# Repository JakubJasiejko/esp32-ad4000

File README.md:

# esp32-ad4000

Driver for the `AD4000` ADC on ESP32. The library handles device configuration and fast raw sample reads over SPI.

## Features
- initialize the device and SPI bus
- configure the control register
- prepare the interface before measurement
- fast `uint16_t` raw data reads

## Dependencies
- `esp32-spi2-bus`

## Files
- `include/ad4000.h`
- `src/ad4000.c`

## Quick start
```c
#include "ad4000.h"

void app_main(void)
{
    spi2_init_bus(SPI2_BUS1, SPI3_HOST, AD4000_PIN_SDI, AD4000_PIN_SDO, AD4000_PIN_SCLK);

    int adc = -1;
    ad4000_init(SPI2_BUS1, &adc, 0, GPIO_NUM_NC, AD4000_PIN_CNV, AD4000_SPI_CLK_HZ, 0);
    ad4000_prepareBeforeMeasurement(adc, AD4000_PIN_SDI);
    uint16_t raw = ad4000_getRawData(adc, AD4000_PIN_CNV);
    (void)raw;
}
```

See `examples/basic_usage/basic_usage.c` for a complete example.

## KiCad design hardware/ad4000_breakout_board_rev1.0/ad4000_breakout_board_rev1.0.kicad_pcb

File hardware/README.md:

# Hardware — esp32-ad4000

Zachowane dostarczone projekty sprzętowe:

- [ad4000_breakout_board_rev1.0](ad4000_breakout_board_rev1.0/ad4000_breakout_board_rev1.0.kicad_pro)

Nazwy plików i odwołania bibliotek zachowano. Numer w nazwie płytki jest oznaczeniem źródłowym; sam w sobie nie oznacza istnienia gałęzi Git o tej nazwie. Migracja standardu nie jest kwalifikacją do produkcji.

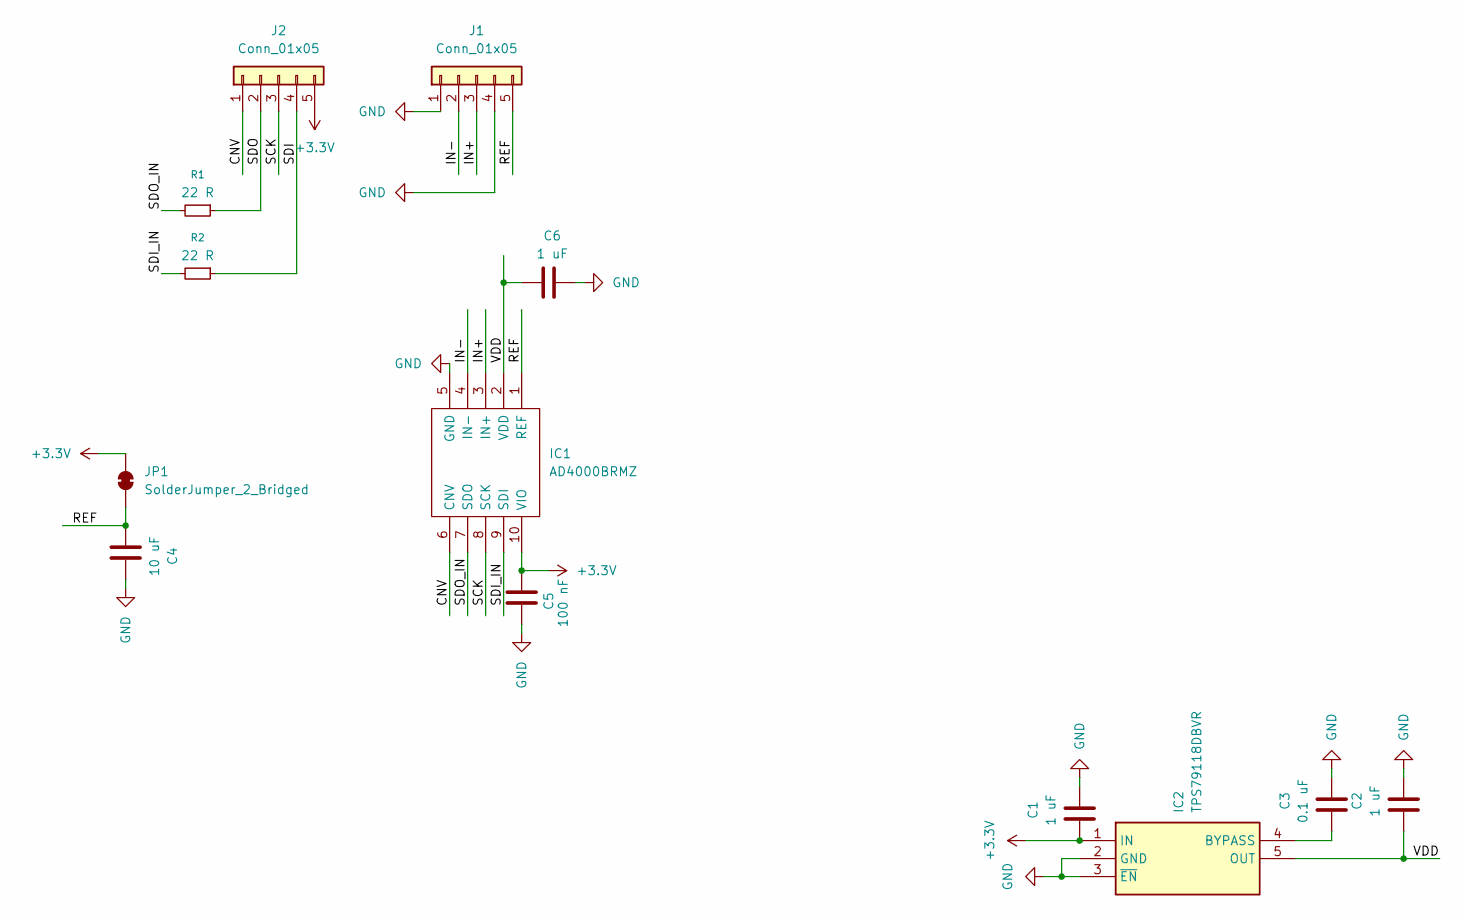
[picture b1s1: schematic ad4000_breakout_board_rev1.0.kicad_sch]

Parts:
C1, C2, C6: 1 uF; C_0402_1005Metric_Pad0.74x0.62mm_HandSolder
C3: 0.1 uF; C_0402_1005Metric_Pad0.74x0.62mm_HandSolder
C4: 10 uF; C_0603_1608Metric_Pad1.08x0.95mm_HandSolder
C5: 100 nF; C_0402_1005Metric_Pad0.74x0.62mm_HandSolder
IC1: AD4000BRMZ; SOP50P490X110-10N; Mouser Part Number 584-AD4000BRMZ
IC2: TPS79118DBVR; SOT95P280X145-5N; Mouser Part Number 595-TPS79118DBVR
J1, J2: Conn_01x05; PinHeader_1x05_P2.54mm_Vertical
JP1: SolderJumper_2_Bridged; SolderJumper-2_P1.3mm_Bridged2Bar_RoundedPad1.0x1.5mm
R1, R2: 22 R; R_0402_1005Metric_Pad0.72x0.64mm_HandSolder

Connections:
+3.3V: C1.1, C5.1, IC1.10 (VIO), IC2.1 (IN), J2.5, JP1.2 (B)
/CNV: IC1.6 (CNV), J2.1
/IN+: IC1.3 (IN+), J1.3
/IN-: IC1.4 (IN-), J1.2
/REF: C4.1, IC1.1 (REF), J1.5, JP1.1 (A)
/SCK: IC1.8 (SCK), J2.3
/SDI: J2.4, R2.1
/SDI_IN: IC1.9 (SDI), R2.2
/SDO: J2.2, R1.1
/SDO_IN: IC1.7 (SDO), R1.2
/VDD: C2.1, C6.1, IC1.2 (VDD), IC2.5 (OUT)
GND: C1.2, C2.2, C3.2, C4.2, C5.2, C6.2, IC1.5 (GND), IC2.2 (GND), IC2.3 (~EN), J1.1, J1.4
unnamed: C3.1, IC2.4 (BYPASS)

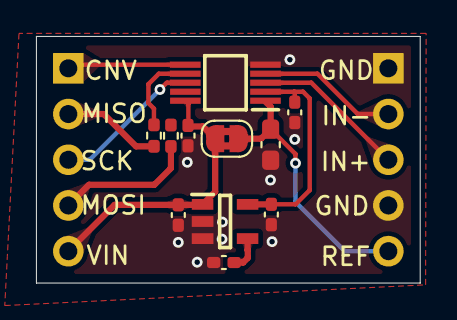
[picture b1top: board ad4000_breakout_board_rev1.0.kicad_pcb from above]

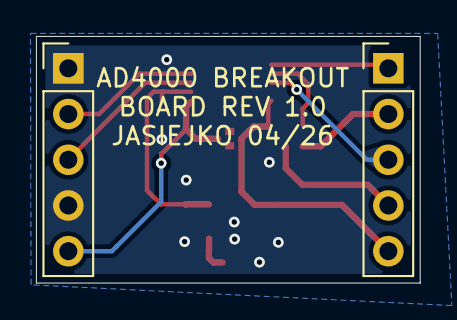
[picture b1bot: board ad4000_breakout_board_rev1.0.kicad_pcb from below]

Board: 2 copper layers, 21.3 x 13.7 mm, 13 parts (2 on the bottom side), 13 nets.

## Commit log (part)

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2026-04-05 Initial component import
2026-04-05 Translate docs and public API comments to English
2026-04-05 Translate source comments and expand Doxygen docs
